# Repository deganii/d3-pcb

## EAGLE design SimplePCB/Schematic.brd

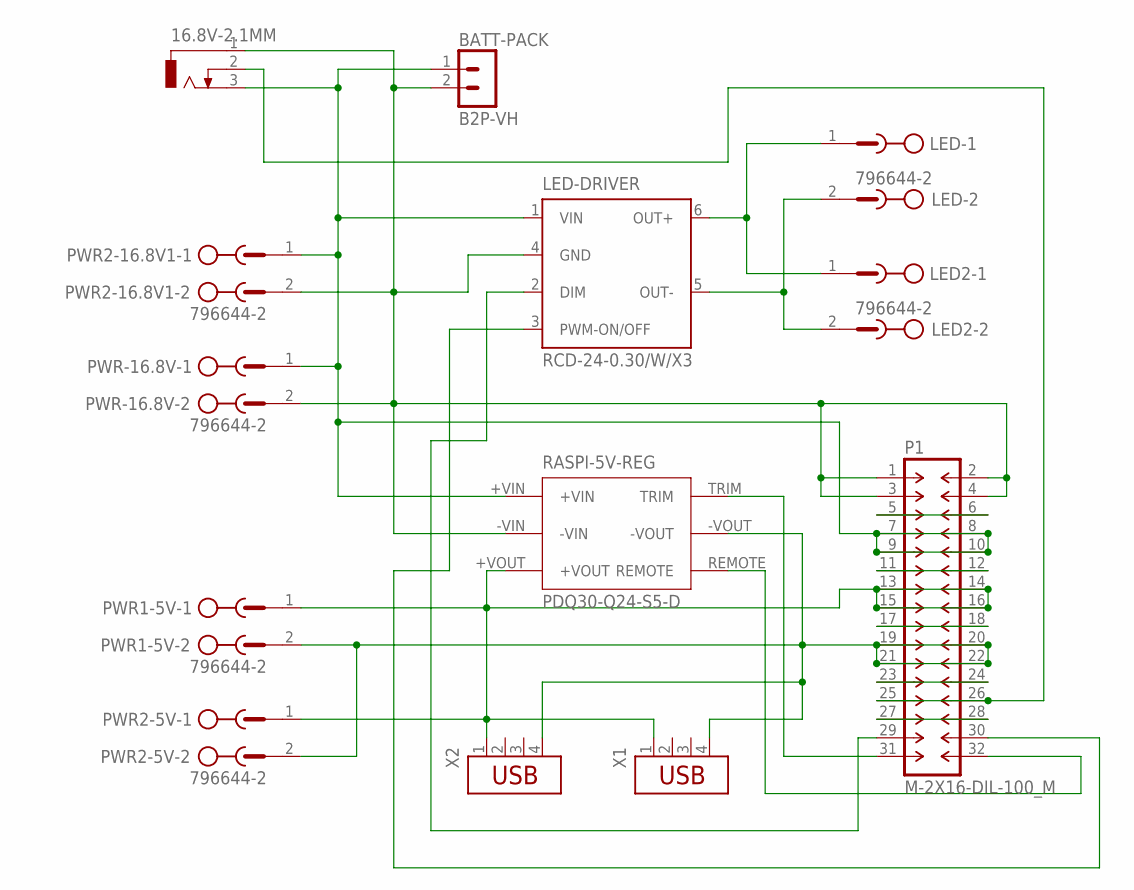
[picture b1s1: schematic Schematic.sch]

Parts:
16.8V-2.1MM: DCJ0303
BATT-PACK: B2P-VH
LED, LED2: 796644-2
LED-DRIVER: RCD-24-0.30/W/X3; RCD-24/W/X3
P1: M-2X16-DIL-100_M; DIL-100-2X16_M
PWR1-5V, PWR2-5V, PWR2-16.8V1: 796644-2
PWR-16.8V: 796644-2
RASPI-5V-REG: PDQ30-Q24-S5-D
X1, X2: USB-787616; USB

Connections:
5VOUT+: P1.13, P1.14, P1.15, P1.16, PWR1-5V.1, PWR2-5V.1, RASPI-5V-REG.+VOUT, X1.1, X2.1
5VOUT-: P1.19, P1.20, P1.21, P1.22, PWR1-5V.2, PWR2-5V.2, RASPI-5V-REG.-VOUT, X1.4, X2.4
BAT+: 16.8V-2.1MM.3, BATT-PACK.1, LED-DRIVER.1 (VIN), P1.7, P1.8, P1.9, P1.10, PWR2-16.8V1.1, PWR-16.8V.1, RASPI-5V-REG.+VIN
BAT-: 16.8V-2.1MM.1, BATT-PACK.2, LED-DRIVER.4 (GND), P1.1, P1.2, P1.3, P1.4, PWR2-16.8V1.2, PWR-16.8V.2, RASPI-5V-REG.-VIN
DIM: LED-DRIVER.2 (DIM), P1.29
LED+: LED.1, LED2.1, LED-DRIVER.6 (OUT+)
LED-: LED.2, LED2.2, LED-DRIVER.5 (OUT-)
unnamed: P1.23, P1.24
unnamed: P1.5, P1.6
unnamed: 16.8V-2.1MM.2, P1.25, P1.26
unnamed: P1.27, P1.28
unnamed: P1.11, P1.12
unnamed: P1.17, P1.18
PWM: LED-DRIVER.3 (PWM-ON/OFF), P1.30
REMOTE: P1.32, RASPI-5V-REG.REMOTE
TRIM: P1.31, RASPI-5V-REG.TRIM

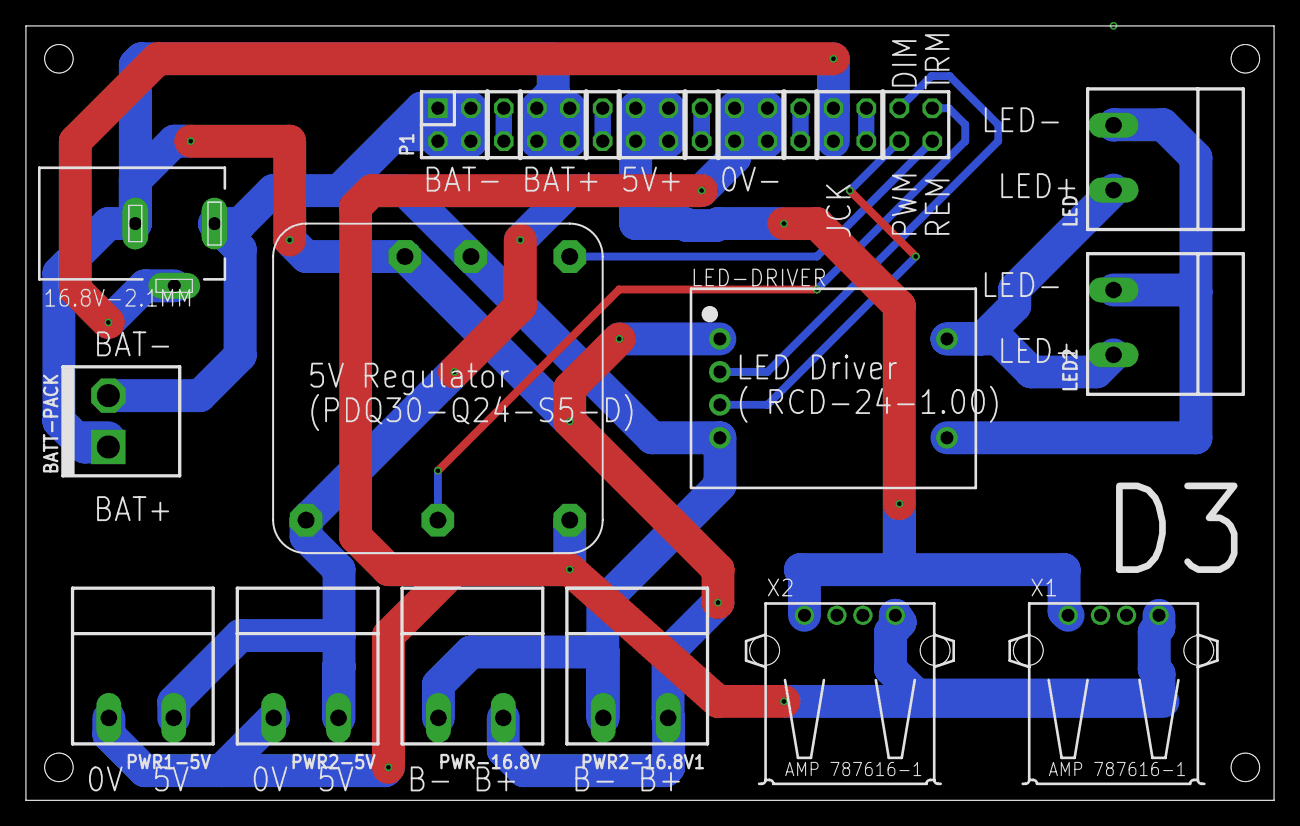
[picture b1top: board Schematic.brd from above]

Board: 2 copper layers, 96.2 x 59.7 mm, 13 parts (0 on the bottom side), 16 nets.

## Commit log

2018-05-28 Initial Checkin - Board Revision 1

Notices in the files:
parts and their libraries:
con-jst-vh: Copyright (C) 2016, Bob Starr
con-amp-termi-block: Copyright (C) 2008, Bob Starr
